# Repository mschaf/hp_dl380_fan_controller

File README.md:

## HP DL380 Fan Controller

A fan controller for my DL380e gen8, should work with similar servers as well. It takes the fan signal from the mainboard and divides it by 2, expect it is over 70% then it just passed it as it is. 

It gets its power and commands from the internal USB port of the server. It acts like a serial device and can be configured via the serial console. 

Firmware for the PIC microcontroller is written with MPLAB X in c.
The PCB layout is made in KiCAD and can be ordered from services like JLCPCB with the files from the gerbers directory.

Its not perfect, there are still some features it should have, like saving the config to survive a power cylce.

The cables needed can either be hacked together with some spare fan cables from HP or made yourself. The connectors are somewhat custom, or at least I could not find them online. You can use 2mm pitch standart pin sockets and grind them down a litte ti fit in the header on the mainbaord.

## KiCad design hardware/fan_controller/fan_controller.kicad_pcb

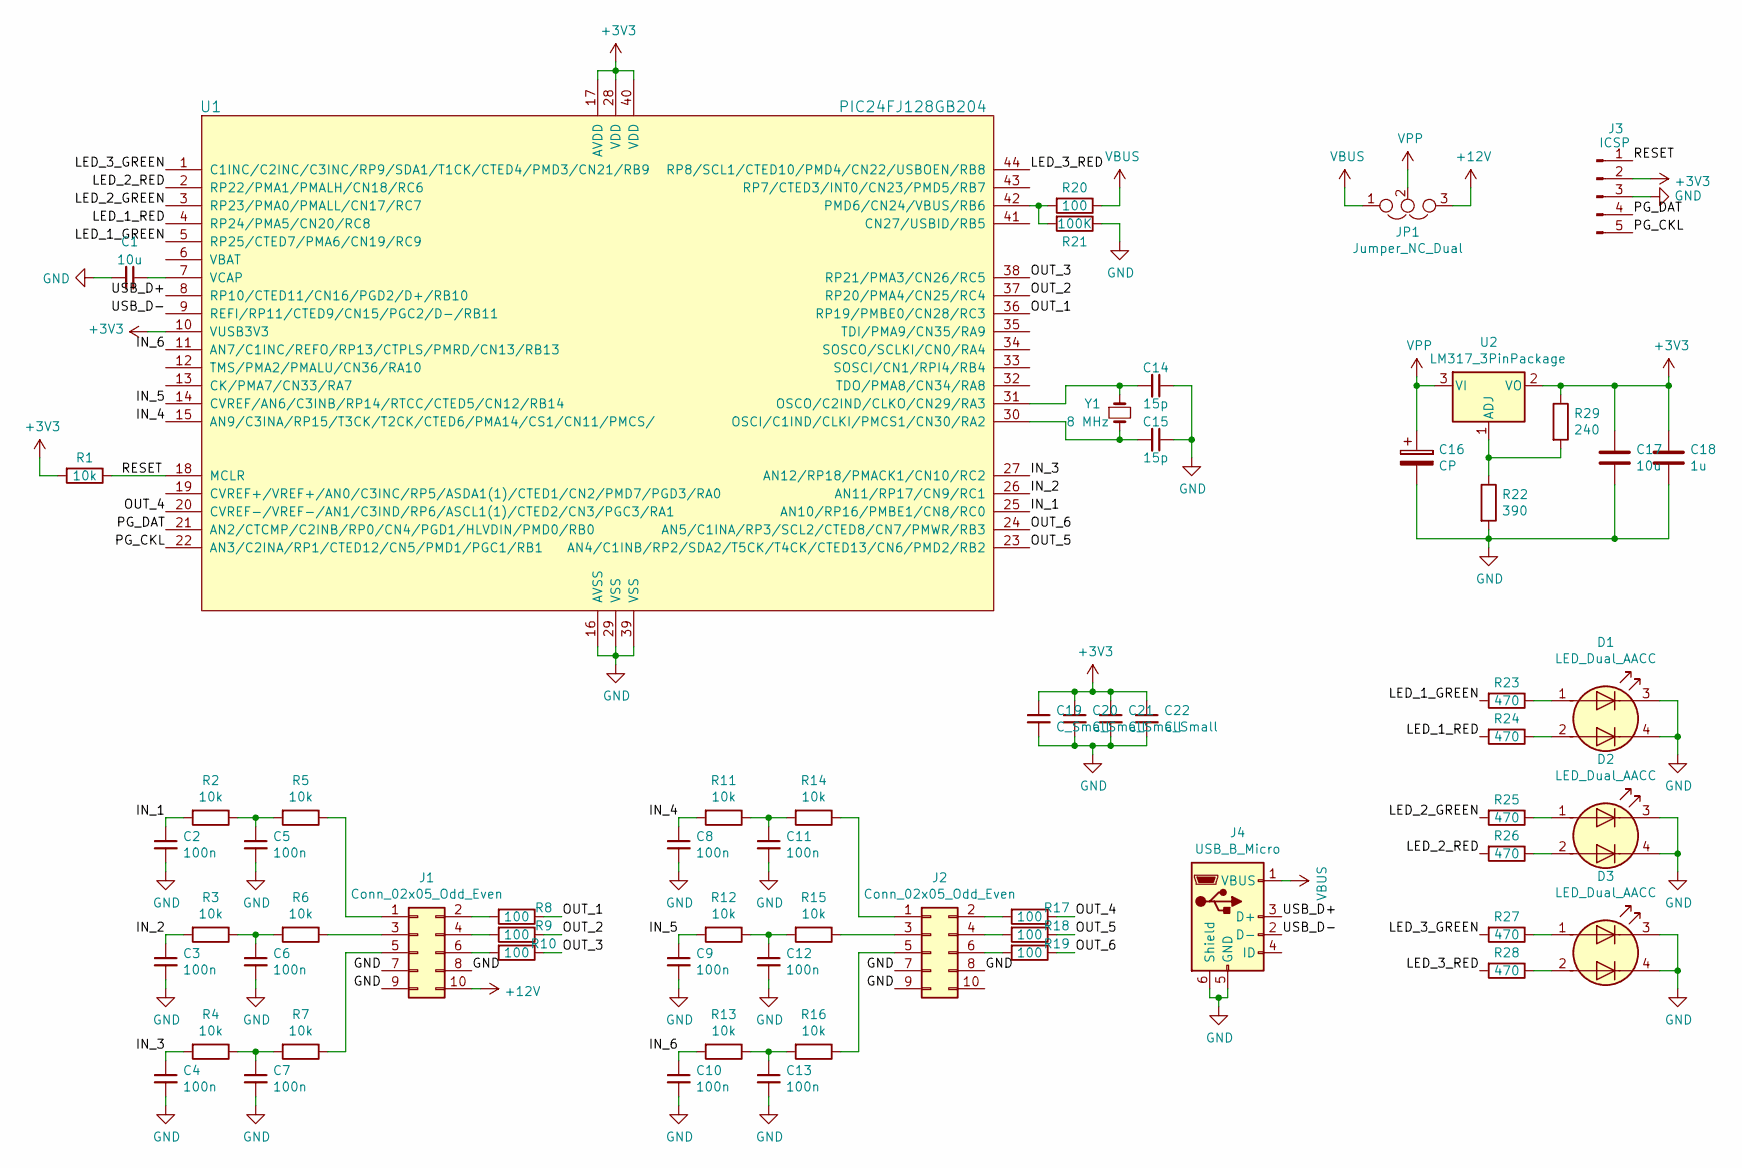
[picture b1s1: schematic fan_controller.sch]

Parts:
C1, C17: 10u; C_1206_3216Metric
C2, C3, C4, C5, C6, C7, C8, C9, C10, C11, C12, C13: 100n; C_0805_2012Metric
C14, C15: 15p; C_0805_2012Metric
C16: CP; CP_Elec_4x5.4
C18: 1u; C_0805_2012Metric
C19, C20, C21, C22: C_Small; C_0805_2012Metric
D1, D2, D3: LED_Dual_AACC; EVL 15-22 R6G6C
J1, J2: Conn_02x05_Odd_Even; IDC-Header_2x05_P2.54mm_Vertical
J3: ICSP; PinSocket_1x05_P2.54mm_Vertical
J4: USB_B_Micro; USB_BWM
JP1: Jumper_NC_Dual; PinSocket_1x03_P2.54mm_Vertical
R1, R2, R3, R4, R5, R6, R7, R11, R12, R13, R14, R15, R16: 10k; R_0805_2012Metric
R8, R9, R10, R17, R18, R19, R20: 100; R_0805_2012Metric
R21: 100K; R_0805_2012Metric
R22: 390; R_0805_2012Metric
R23, R24, R25, R26, R27, R28: 470; R_0805_2012Metric
R29: 240; R_0805_2012Metric
U1: PIC24FJ128GB204; TQFP-44_10x10mm_P0.8mm
U2: LM317_3PinPackage; SOT-223-3_TabPin2
Y1: 8 MHz; smd_quarz

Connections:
+3V3: C17.1, C18.1, C19.1, C20.1, C21.1, C22.1, J3.2, R1.2, R29.1, U1.10 (VUSB3V3), U1.17 (AVDD), U1.28 (VDD), U1.40 (VDD), U2.2 (VO)
+12V: J1.10, JP1.3
/IN_1: C2.1, R2.2, U1.25 (AN10/RP16/PMBE1/CN8/RC0)
/IN_2: C3.1, R3.2, U1.26 (AN11/RP17/CN9/RC1)
/IN_3: C4.1, R4.2, U1.27 (AN12/RP18/PMACK1/CN10/RC2)
/IN_4: C8.1, R11.2, U1.15 (AN9/C3INA/RP15/T3CK/T2CK/CTED6/PMA14/CS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)
/IN_5: C9.1, R12.2, U1.14 (CVREF/AN6/C3INB/RP14/RTCC/CTED5/CN12/RB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)
/IN_6: C10.1, R13.2, U1.11 (AN7/C1INC/REFO/RP13/CTPLS/PMRD/CN13/RB13)
/LED_1_GREEN: R23.2, U1.5 (RP25/CTED7/PMA6/CN19/RC9)
/LED_1_RED: R24.2, U1.4 (RP24/PMA5/CN20/RC8)
/LED_2_GREEN: R25.2, U1.3 (RP23/PMA0/PMALL/CN17/RC7)
/LED_2_RED: R26.2, U1.2 (RP22/PMA1/PMALH/CN18/RC6)
/LED_3_GREEN: R27.2, U1.1 (C1INC/C2INC/C3INC/RP9/SDA1/T1CK/CTED4/P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)
/LED_3_RED: R28.2, U1.44 (RP8/SCL1/CTED10/PMD4/CN22/USBOEN/RB8)
/OUT_1: R8.1, U1.36 (RP19/PMBE0/CN28/RC3)
/OUT_2: R9.1, U1.37 (RP20/PMA4/CN25/RC4)
/OUT_3: R10.1, U1.38 (RP21/PMA3/CN26/RC5)
/OUT_4: R17.1, U1.20 (CVREF-/VREF-/AN1/C3IND/RP6/ASCL1(1)/CTE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)
/OUT_5: R18.1, U1.23 (AN4/C1INB/RP2/SDA2/T5CK/T4CK/CTED13/CN6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)
/OUT_6: R19.1, U1.24 (AN5/C1INA/RP3/SCL2/CTED8/CN7/PMWR/RB3)
/PG_CKL: J3.5, U1.22 (AN3/C2INA/RP1/CTED12/CN5/PMD1/PGC1/RB1)
/PG_DAT: J3.4, U1.21 (AN2/CTCMP/C2INB/RP0/CN4/PGD1/HLVDIN/PMD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)
/RESET: J3.1, R1.1, U1.18 (MCLR)
/USB_D+: J4.3 (D+), U1.8 (RP10/CTED11/CN16/PGD2/D+/RB10)
/USB_D-: J4.2 (D-), U1.9 (REFI/RP11/CTED9/CN15/PGC2/D-/RB11)
GND: C1.2, C2.2, C3.2, C4.2, C5.2, C6.2, C7.2, C8.2, C9.2, C10.2, C11.2, C12.2, C13.2, C14.1, C15.1, C16.2, C17.2, C18.2, C19.2, C20.2, C21.2, C22.2, D1.3 (K1), D1.4 (K2), D2.3 (K1), D2.4 (K2), D3.3 (K1), D3.4 (K2), J1.7, J1.8, J1.9, J2.7, J2.8, J2.9, J3.3, J4.5 (GND), J4.6 (Shield), R21.1, R22.2, U1.16 (AVSS), U1.29 (VSS), U1.39 (VSS)
unnamed: C1.1, U1.7 (VCAP)
unnamed: C5.1, R2.1, R5.2
unnamed: C6.1, R3.1, R6.2
unnamed: C7.1, R4.1, R7.2
unnamed: C11.1, R11.1, R14.2
unnamed: C12.1, R12.1, R15.2
unnamed: C13.1, R13.1, R16.2
unnamed: C14.2, U1.31 (OSCO/C2IND/CLKO/CN29/RA3), Y1.1
unnamed: C15.2, U1.30 (OSCI/C1IND/CLKI/PMCS1/CN30/RA2), Y1.2
unnamed: D1.1 (A1), R23.1
unnamed: D1.2 (A2), R24.1
unnamed: D2.1 (A1), R25.1
unnamed: D2.2 (A2), R26.1
unnamed: D3.1 (A1), R27.1
unnamed: D3.2 (A2), R28.1
unnamed: J1.1, R5.1
unnamed: J1.2, R8.2
unnamed: J1.3, R6.1
unnamed: J1.4, R9.2
unnamed: J1.5, R7.1
unnamed: J1.6, R10.2
unnamed: J2.1, R14.1
unnamed: J2.2, R17.2
unnamed: J2.3, R15.1
unnamed: J2.4, R18.2
unnamed: J2.5, R16.1
unnamed: J2.6, R19.2
unnamed: R20.2, R21.2, U1.42 (PMD6/CN24/VBUS/RB6)
unnamed: R22.1, R29.2, U2.1 (ADJ)
VBUS: J4.1 (VBUS), JP1.1, R20.1
VPP: C16.1, JP1.2, U2.3 (VI)

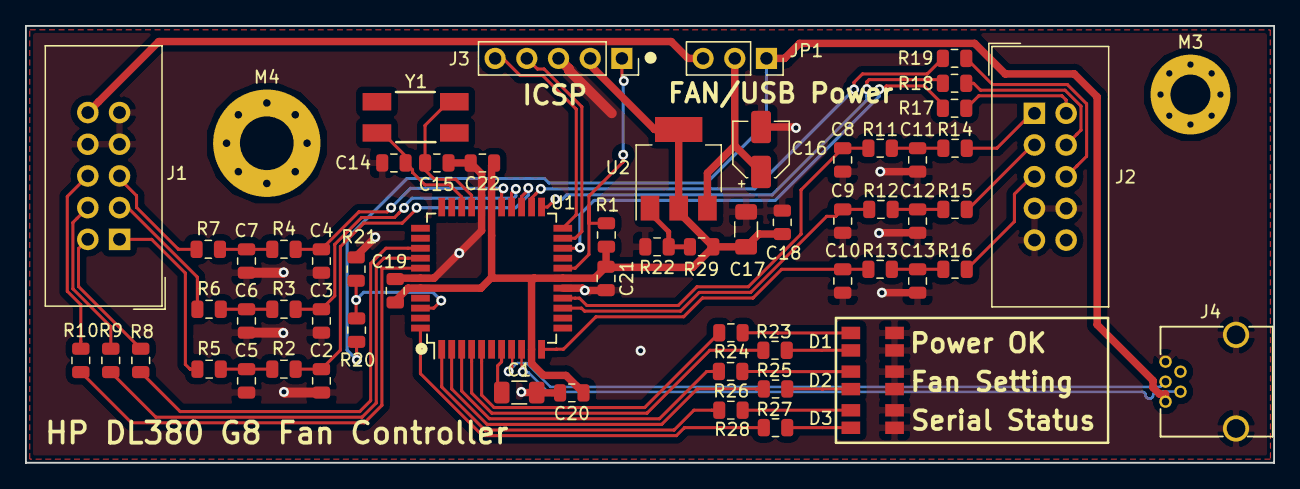
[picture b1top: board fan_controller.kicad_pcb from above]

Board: 2 copper layers, 100.0 x 35.0 mm, 64 parts (0 on the bottom side), 57 nets.

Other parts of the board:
M3: MountingHole_3.2mm_M3_Pad_Via
M4: MountingHole_4.3mm_M4_Pad_Via

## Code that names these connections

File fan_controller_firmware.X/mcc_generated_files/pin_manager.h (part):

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*/
/**
  @Summary
    Sets the GPIO pin, RB13, high using LATB13.

  @Description
    Sets the GPIO pin, RB13, high using LATB13.

  @Preconditions
    The RB13 must be set to an output.
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#define LED_SetHigh()          _LATB13 = 1
/**
  @Summary
    Sets the GPIO pin, RB13, low using LATB13.

  @Description
    Sets the GPIO pin, RB13, low using LATB13.

  @Preconditions
    The RB13 must be set to an output.
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#define LED_SetLow()           _LATB13 = 0
/**
  @Summary
    Toggles the GPIO pin, RB13, using LATB13.

  @Description
    Toggles the GPIO pin, RB13, using LATB13.

  @Preconditions
    The RB13 must be set to an output.
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#define LED_Toggle()           _LATB13 ^= 1
/**
  @Summary
    Reads the value of the GPIO pin, RB13.

  @Description
    Reads the value of the GPIO pin, RB13.

  @Preconditions
    None.
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    </code>

*/
#define LED_GetValue()         _RB13
/**
  @Summary
    Configures the GPIO pin, RB13, as an input.

  @Description
    Configures the GPIO pin, RB13, as an input.

  @Preconditions
    None.
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#define LED_SetDigitalInput()  _TRISB13 = 1
/**
  @Summary
    Configures the GPIO pin, RB13, as an output.

  @Description
    Configures the GPIO pin, RB13, as an output.

  @Preconditions
    None.
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#define LED_SetDigitalOutput() _TRISB13 = 0
/**
  @Summary
    Sets the GPIO pin, RB8, high using LATB8.

  @Description
    Sets the GPIO pin, RB8, high using LATB8.

  @Preconditions
    The RB8 must be set to an output.
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#define led_serial_red_SetHigh()          _LATB8 = 1
/**
  @Summary
    Sets the GPIO pin, RB8, low using LATB8.

  @Description
    Sets the GPIO pin, RB8, low using LATB8.

  @Preconditions
    The RB8 must be set to an output.
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#define led_serial_red_SetLow()           _LATB8 = 0
/**
  @Summary
    Toggles the GPIO pin, RB8, using LATB8.

  @Description
    Toggles the GPIO pin, RB8, using LATB8.

  @Preconditions
    The RB8 must be set to an output.
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#define led_serial_red_Toggle()           _LATB8 ^= 1
/**
  @Summary
    Reads the value of the GPIO pin, RB8.

  @Description
    Reads the value of the GPIO pin, RB8.

  @Preconditions
    None.
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    </code>

*/
#define led_serial_red_GetValue()         _RB8
/**
  @Summary
    Configures the GPIO pin, RB8, as an input.

  @Description
    Configures the GPIO pin, RB8, as an input.

  @Preconditions
    None.
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#define led_serial_red_SetDigitalInput()  _TRISB8 = 1
/**
  @Summary
    Configures the GPIO pin, RB8, as an output.

  @Description
    Configures the GPIO pin, RB8, as an output.

  @Preconditions
    None.
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#define led_serial_red_SetDigitalOutput() _TRISB8 = 0
/**
  @Summary
    Sets the GPIO pin, RB9, high using LATB9.

  @Description
    Sets the GPIO pin, RB9, high using LATB9.

  @Preconditions
    The RB9 must be set to an output.
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#define led_serial_green_SetHigh()          _LATB9 = 1
/**
  @Summary
    Sets the GPIO pin, RB9, low using LATB9.

  @Description
    Sets the GPIO pin, RB9, low using LATB9.

  @Preconditions
    The RB9 must be set to an output.
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#define led_serial_green_SetLow()           _LATB9 = 0
/**
  @Summary
    Toggles the GPIO pin, RB9, using LATB9.

  @Description
    Toggles the GPIO pin, RB9, using LATB9.

  @Preconditions
    The RB9 must be set to an output.
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#define led_serial_green_Toggle()           _LATB9 ^= 1
/**
  @Summary
    Reads the value of the GPIO pin, RB9.

  @Description
    Reads the value of the GPIO pin, RB9.

  @Preconditions
    None.
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    </code>

*/
#define led_serial_green_GetValue()         _RB9
/**
  @Summary
    Configures the GPIO pin, RB9, as an input.

  @Description
    Configures the GPIO pin, RB9, as an input.

  @Preconditions
    None.
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#define led_serial_green_SetDigitalInput()  _TRISB9 = 1
/**
  @Summary
    Configures the GPIO pin, RB9, as an output.

  @Description
    Configures the GPIO pin, RB9, as an output.

  @Preconditions
    None.
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#define led_serial_green_SetDigitalOutput() _TRISB9 = 0
/**
  @Summary
    Sets the GPIO pin, RC6, high using LATC6.

  @Description
    Sets the GPIO pin, RC6, high using LATC6.

  @Preconditions
    The RC6 must be set to an output.
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#define led_fan_red_SetHigh()          _LATC6 = 1
/**
  @Summary
    Sets the GPIO pin, RC6, low using LATC6.

  @Description
    Sets the GPIO pin, RC6, low using LATC6.

  @Preconditions
    The RC6 must be set to an output.
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#define led_fan_red_SetLow()           _LATC6 = 0
/**
  @Summary
    Toggles the GPIO pin, RC6, using LATC6.

  @Description
    Toggles the GPIO pin, RC6, using LATC6.

  @Preconditions
    The RC6 must be set to an output.
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#define led_fan_red_Toggle()           _LATC6 ^= 1
/**
  @Summary
    Reads the value of the GPIO pin, RC6.

  @Description
    Reads the value of the GPIO pin, RC6.

  @Preconditions
    None.
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    </code>

*/
#define led_fan_red_GetValue()         _RC6
/**
  @Summary
    Configures the GPIO pin, RC6, as an input.

  @Description
    Configures the GPIO pin, RC6, as an input.

  @Preconditions
    None.
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#define led_fan_red_SetDigitalInput()  _TRISC6 = 1
/**
  @Summary
    Configures the GPIO pin, RC6, as an output.

  @Description
    Configures the GPIO pin, RC6, as an output.

  @Preconditions
    None.
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#define led_fan_red_SetDigitalOutput() _TRISC6 = 0
/**
  @Summary
    Sets the GPIO pin, RC7, high using LATC7.

  @Description
    Sets the GPIO pin, RC7, high using LATC7.

  @Preconditions
    The RC7 must be set to an output.
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#define led_fan_green_SetHigh()          _LATC7 = 1
/**
  @Summary
    Sets the GPIO pin, RC7, low using LATC7.

  @Description
    Sets the GPIO pin, RC7, low using LATC7.

  @Preconditions
    The RC7 must be set to an output.
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#define led_fan_green_SetLow()           _LATC7 = 0
/**
  @Summary
    Toggles the GPIO pin, RC7, using LATC7.

  @Description
    Toggles the GPIO pin, RC7, using LATC7.

  @Preconditions
    The RC7 must be set to an output.
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#define led_fan_green_Toggle()           _LATC7 ^= 1
/**
  @Summary
    Reads the value of the GPIO pin, RC7.

  @Description
    Reads the value of the GPIO pin, RC7.

  @Preconditions
    None.
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    </code>

*/
#define led_fan_green_GetValue()         _RC7
/**
  @Summary
    Configures the GPIO pin, RC7, as an input.

  @Description
    Configures the GPIO pin, RC7, as an input.

  @Preconditions
    None.
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#define led_fan_green_SetDigitalInput()  _TRISC7 = 1
/**
  @Summary
    Configures the GPIO pin, RC7, as an output.

  @Description
    Configures the GPIO pin, RC7, as an output.

  @Preconditions
    None.
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#define led_fan_green_SetDigitalOutput() _TRISC7 = 0
/**
  @Summary
    Sets the GPIO pin, RC8, high using LATC8.

  @Description
    Sets the GPIO pin, RC8, high using LATC8.

  @Preconditions
    The RC8 must be set to an output.
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#define led_power_red_SetHigh()          _LATC8 = 1
/**
  @Summary
    Sets the GPIO pin, RC8, low using LATC8.

  @Description
    Sets the GPIO pin, RC8, low using LATC8.

  @Preconditions
    The RC8 must be set to an output.
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#define led_power_red_SetLow()           _LATC8 = 0
/**
  @Summary
    Toggles the GPIO pin, RC8, using LATC8.

  @Description
    Toggles the GPIO pin, RC8, using LATC8.

  @Preconditions
    The RC8 must be set to an output.
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#define led_power_red_Toggle()           _LATC8 ^= 1
/**
  @Summary
    Reads the value of the GPIO pin, RC8.

  @Description
    Reads the value of the GPIO pin, RC8.

  @Preconditions
    None.
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    </code>

*/
#define led_power_red_GetValue()         _RC8
/**
  @Summary
    Configures the GPIO pin, RC8, as an input.

  @Description
    Configures the GPIO pin, RC8, as an input.

  @Preconditions
    None.
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#define led_power_red_SetDigitalInput()  _TRISC8 = 1
/**
  @Summary
    Configures the GPIO pin, RC8, as an output.

  @Description
    Configures the GPIO pin, RC8, as an output.

  @Preconditions
    None.
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#define led_power_red_SetDigitalOutput() _TRISC8 = 0
/**
  @Summary
    Sets the GPIO pin, RC9, high using LATC9.

  @Description
    Sets the GPIO pin, RC9, high using LATC9.

  @Preconditions
    The RC9 must be set to an output.
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#define led_power_green_SetHigh()          _LATC9 = 1
/**
  @Summary
    Sets the GPIO pin, RC9, low using LATC9.

  @Description
    Sets the GPIO pin, RC9, low using LATC9.

  @Preconditions
    The RC9 must be set to an output.
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#define led_power_green_SetLow()           _LATC9 = 0
/**
  @Summary
    Toggles the GPIO pin, RC9, using LATC9.

  @Description
    Toggles the GPIO pin, RC9, using LATC9.

  @Preconditions
    The RC9 must be set to an output.
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#define led_power_green_Toggle()           _LATC9 ^= 1
/**
  @Summary
    Reads the value of the GPIO pin, RC9.

  @Description
    Reads the value of the GPIO pin, RC9.

  @Preconditions
    None.
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    </code>

*/
#define led_power_green_GetValue()         _RC9
/**
  @Summary
    Configures the GPIO pin, RC9, as an input.

  @Description
    Configures the GPIO pin, RC9, as an input.

  @Preconditions
    None.
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#define led_power_green_SetDigitalInput()  _TRISC9 = 1
/**
  @Summary
    Configures the GPIO pin, RC9, as an output.

  @Description
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
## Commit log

2020-05-13 Init Commit
2020-05-13 add readme
2020-05-13 add updated firmware version

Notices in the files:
fan_controller_firmware.X/mcc_generated_files/pin_manager.h:
(c) 2016 Microchip Technology Inc. and its subsidiaries. You may use this
